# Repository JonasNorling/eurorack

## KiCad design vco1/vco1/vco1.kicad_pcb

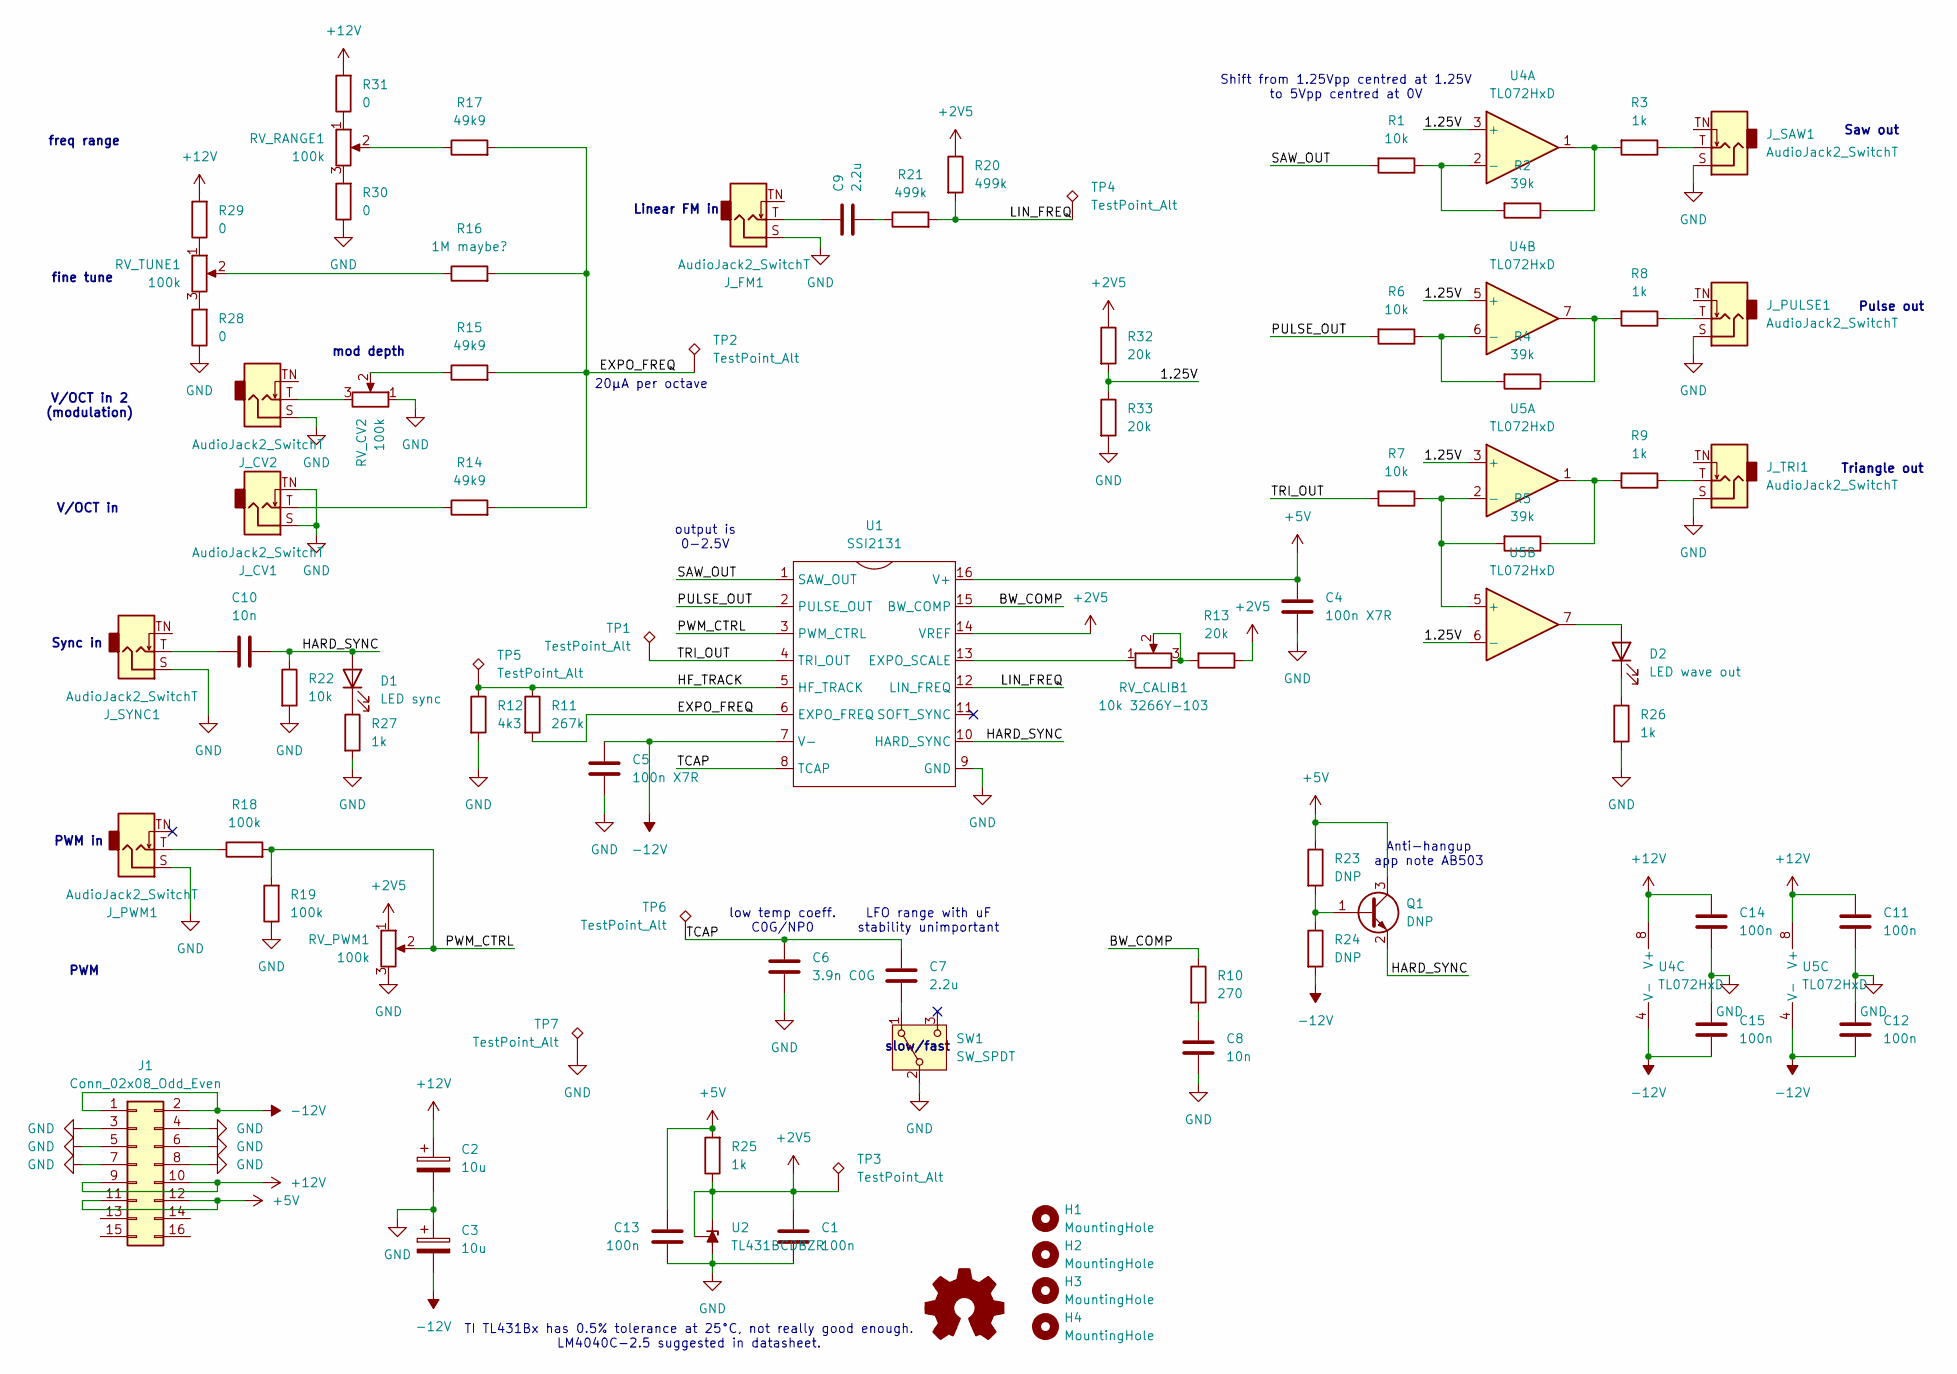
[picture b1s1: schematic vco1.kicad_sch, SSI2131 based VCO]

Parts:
C1, C11, C12, C13, C14, C15: 100n; C_0603_1608Metric_Pad1.08x0.95mm_HandSolder
C2, C3: 10u; CP_Radial_D5.0mm_P2.50mm
C4, C5: 100n X7R; C_0603_1608Metric_Pad1.08x0.95mm_HandSolder
C6: 3.9n C0G; C_0603_1608Metric_Pad1.08x0.95mm_HandSolder
C7, C9: 2.2u; C_0805_2012Metric_Pad1.18x1.45mm_HandSolder
C8, C10: 10n; C_0603_1608Metric_Pad1.08x0.95mm_HandSolder
D1: LED sync; LED_D3.0mm
D2: LED wave out; LED_D3.0mm
H1, H2, H3, H4: MountingHole; MountingHole_3.5mm
J1: Conn_02x08_Odd_Even; IDC-Header_2x08_P2.54mm_Vertical
J_CV1, J_CV2: AudioJack2_SwitchT; Jack_3.5mm_QingPu_WQP-PJ398SM_Vertical_CircularHoles
J_FM1: AudioJack2_SwitchT; Jack_3.5mm_QingPu_WQP-PJ398SM_Vertical_CircularHoles
J_PULSE1: AudioJack2_SwitchT; Jack_3.5mm_QingPu_WQP-PJ398SM_Vertical_CircularHoles
J_PWM1: AudioJack2_SwitchT; Jack_3.5mm_QingPu_WQP-PJ398SM_Vertical_CircularHoles
J_SAW1: AudioJack2_SwitchT; Jack_3.5mm_QingPu_WQP-PJ398SM_Vertical_CircularHoles
J_SYNC1: AudioJack2_SwitchT; Jack_3.5mm_QingPu_WQP-PJ398SM_Vertical_CircularHoles
J_TRI1: AudioJack2_SwitchT; Jack_3.5mm_QingPu_WQP-PJ398SM_Vertical_CircularHoles
Q1: DNP; SOT-23
R1, R6, R7, R22: 10k; R_0603_1608Metric_Pad0.98x0.95mm_HandSolder
R2, R4, R5: 39k; R_0603_1608Metric_Pad0.98x0.95mm_HandSolder
R3, R8, R9, R25, R26, R27: 1k; R_0603_1608Metric_Pad0.98x0.95mm_HandSolder
R10: 270; R_0603_1608Metric_Pad0.98x0.95mm_HandSolder
R11: 267k; R_0603_1608Metric_Pad0.98x0.95mm_HandSolder
R12: 4k3; R_0603_1608Metric_Pad0.98x0.95mm_HandSolder
R13, R32, R33: 20k; R_0603_1608Metric_Pad0.98x0.95mm_HandSolder
R14, R15, R17: 49k9; R_0603_1608Metric_Pad0.98x0.95mm_HandSolder
R16: 1M maybe?; R_0603_1608Metric_Pad0.98x0.95mm_HandSolder
R18, R19: 100k; R_0603_1608Metric_Pad0.98x0.95mm_HandSolder
R20, R21: 499k; R_0603_1608Metric_Pad0.98x0.95mm_HandSolder
R23, R24: DNP; R_0603_1608Metric_Pad0.98x0.95mm_HandSolder
R28, R29, R30, R31: 0; R_0603_1608Metric_Pad0.98x0.95mm_HandSolder
RV_CALIB1: 10k 3266Y-103; Potentiometer_Bourns_3266Y_Vertical
RV_CV2: 100k; RV9012NO
RV_PWM1: 100k; RV9012NO
RV_RANGE1: 100k; RV9012NO
RV_TUNE1: 100k; RV9012NO
SW1: SW_SPDT; SPDT big pads
TP1, TP2, TP3, TP4, TP5, TP6, TP7: TestPoint_Alt; TP_0.9mm
U1: SSI2131; STC_SOP-16_3.9x9.9mm_P1.27mm
U2: TL431BCDBZR; SOT-23
U4, U5: TL072HxD; SOIC-8_3.9x4.9mm_P1.27mm

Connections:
+2V5: C1.1, R13.1, R20.1, R25.1, R32.1, RV_PWM1.1, TP3.1, U1.14 (VREF), U2.1 (K), U2.2 (REF)
+5V: C4.1, C13.2, J1.11, J1.12, Q1.3 (C), R23.1, R25.2, U1.16 (V+)
+12V: C2.1, C11.1, C14.1, J1.9, J1.10, R29.2, R31.2, U4.8 (V+), U5.8 (V+)
-12V: C3.2, C5.1, C12.2, C15.2, J1.1, J1.2, R24.2, U1.7 (V-), U4.4 (V-), U5.4 (V-)
/1.25V: R32.2, R33.1, U4.3 (+), U4.5 (+), U5.3 (+), U5.6 (-)
/BW_COMP: R10.1, U1.15 (BW_COMP)
/EXPO_FREQ: R11.2, R14.2, R15.2, R16.2, R17.2, TP2.1, U1.6 (EXPO_FREQ)
/HARD_SYNC: C10.2, D1.2 (A), Q1.2 (E), R22.1, U1.10 (HARD_SYNC)
/HF_TRACK: R11.1, R12.1, TP5.1, U1.5 (HF_TRACK)
/LIN_FREQ: R20.2, R21.2, TP4.1, U1.12 (LIN_FREQ)
/PULSE_OUT: R6.2, U1.2 (PULSE_OUT)
/PWM_CTRL: R18.2, R19.2, RV_PWM1.2, U1.3 (PWM_CTRL)
/SAW_OUT: R1.2, U1.1 (SAW_OUT)
/TCAP: C6.1, C7.1, TP6.1, U1.8 (TCAP)
/TRI_OUT: R7.2, TP1.1, U1.4 (TRI_OUT)
GND: C1.2, C2.2, C3.1, C4.2, C5.2, C6.2, C8.2, C11.2, C12.1, C13.1, C14.2, C15.1, J1.3, J1.4, J1.5, J1.6, J1.7, J1.8, J_CV1.S, J_CV1.TN, J_CV2.S, J_FM1.S, J_PULSE1.S, J_PWM1.S, J_SAW1.S, J_SYNC1.S, J_TRI1.S, R12.2, R19.1, R22.2, R26.2, R27.2, R28.1, R30.1, R33.2, RV_CV2.1, RV_PWM1.3, SW1.2 (B), TP7.1, U1.9 (GND), U2.3 (A)
unnamed: C8.1, R10.2
unnamed: C9.1, J_FM1.T
unnamed: C9.2, R21.1
unnamed: C10.1, J_SYNC1.T
unnamed: D1.1 (K), R27.1
unnamed: D2.2 (A), U5.7
unnamed: D2.1 (K), R26.1
unnamed: J_CV1.T, R14.1
unnamed: J_CV2.T, RV_CV2.3
unnamed: J_PULSE1.T, R8.1
unnamed: J_PWM1.T, R18.1
unnamed: J_SAW1.T, R3.1
unnamed: J_TRI1.T, R9.1
unnamed: Q1.1 (B), R23.2, R24.1
unnamed: R2.1, R3.2, U4.1
unnamed: R4.1, R8.2, U4.7
unnamed: R5.1, R9.2, U5.1
unnamed: R13.2, RV_CALIB1.2, RV_CALIB1.3
unnamed: R15.1, RV_CV2.2
unnamed: R16.1, RV_TUNE1.2
unnamed: R17.1, RV_RANGE1.2
unnamed: R28.2, RV_TUNE1.3
unnamed: R29.1, RV_TUNE1.1
unnamed: R30.2, RV_RANGE1.3
unnamed: R31.1, RV_RANGE1.1
unnamed: C7.2, SW1.1 (A)
unnamed: RV_CALIB1.1, U1.13 (EXPO_SCALE)
unnamed: R1.1, R2.2, U4.2 (-)
unnamed: R4.2, R6.1, U4.6 (-)
unnamed: R5.2, R7.1, U5.2 (-), U5.5 (+)

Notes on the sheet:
slow/fast
mod depth
freq range
LFO range with uF stability unimportant
Linear FM in
PWM in
20µA per octave
low temp coeff. C0G/NP0
Anti-hangup app note AB503
V/OCT in
output is 0-2.5V
PWM
Sync in
TI TL431Bx has 0.5% tolerance at 25°C, not really good enough. LM4040C-2.5 suggested in datasheet.
Shift from 1.25Vpp centred at 1.25V to 5Vpp centred at 0V
Saw out
Pulse out
V/OCT in 2 (modulation)
fine tune
Triangle out

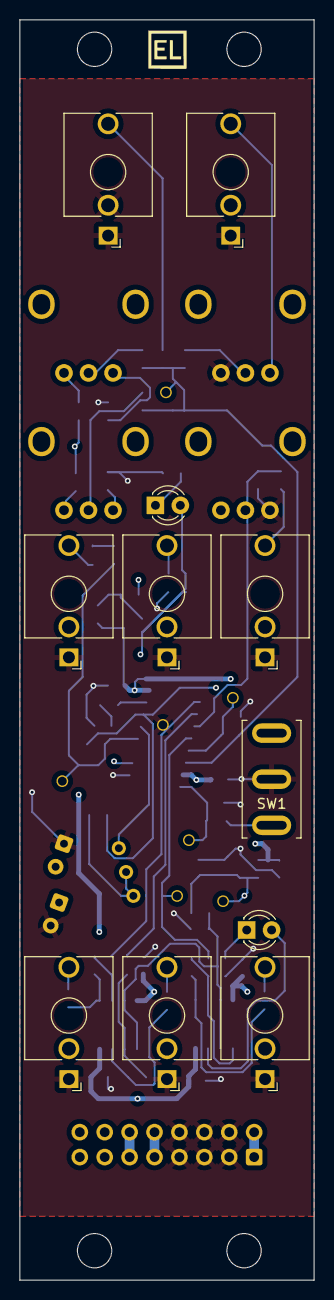
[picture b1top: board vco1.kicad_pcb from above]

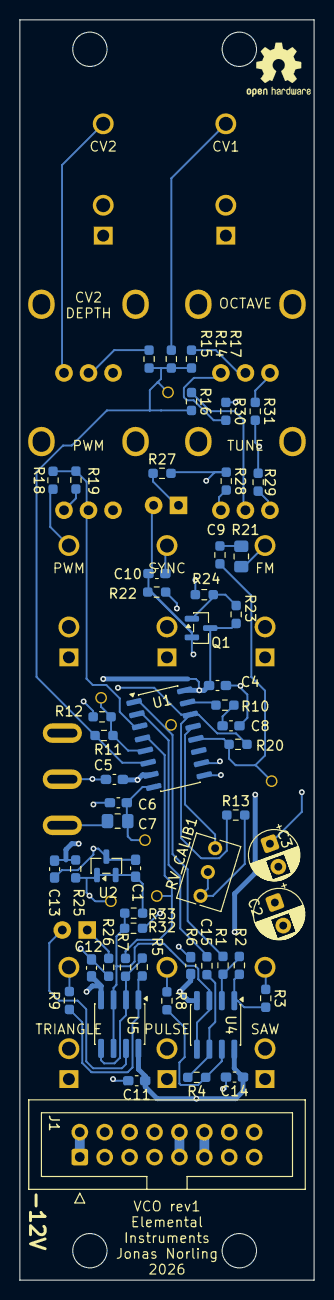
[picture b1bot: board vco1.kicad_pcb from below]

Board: 4 copper layers, 30.0 x 128.5 mm, 81 parts (55 on the bottom side), 46 nets.
